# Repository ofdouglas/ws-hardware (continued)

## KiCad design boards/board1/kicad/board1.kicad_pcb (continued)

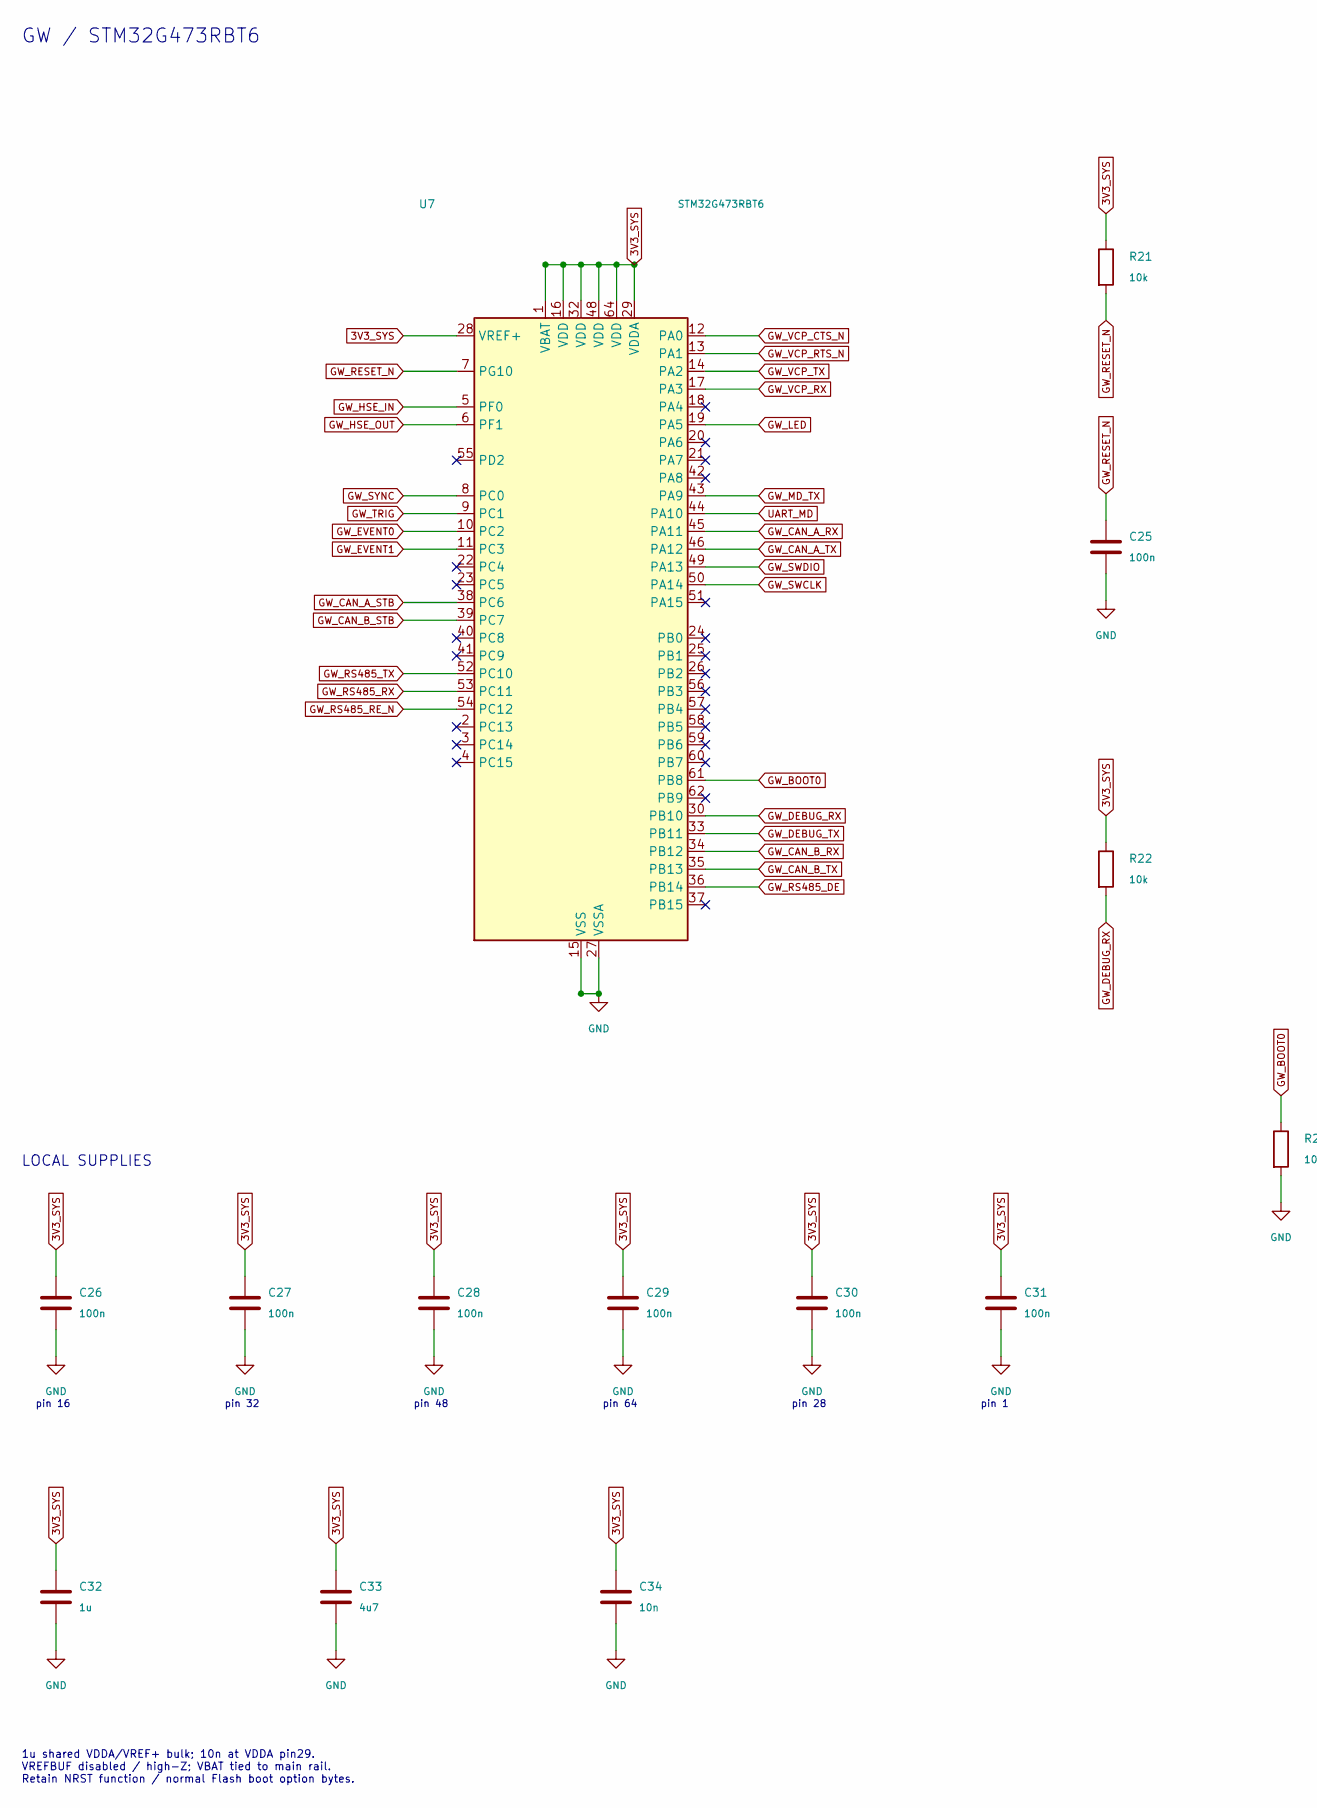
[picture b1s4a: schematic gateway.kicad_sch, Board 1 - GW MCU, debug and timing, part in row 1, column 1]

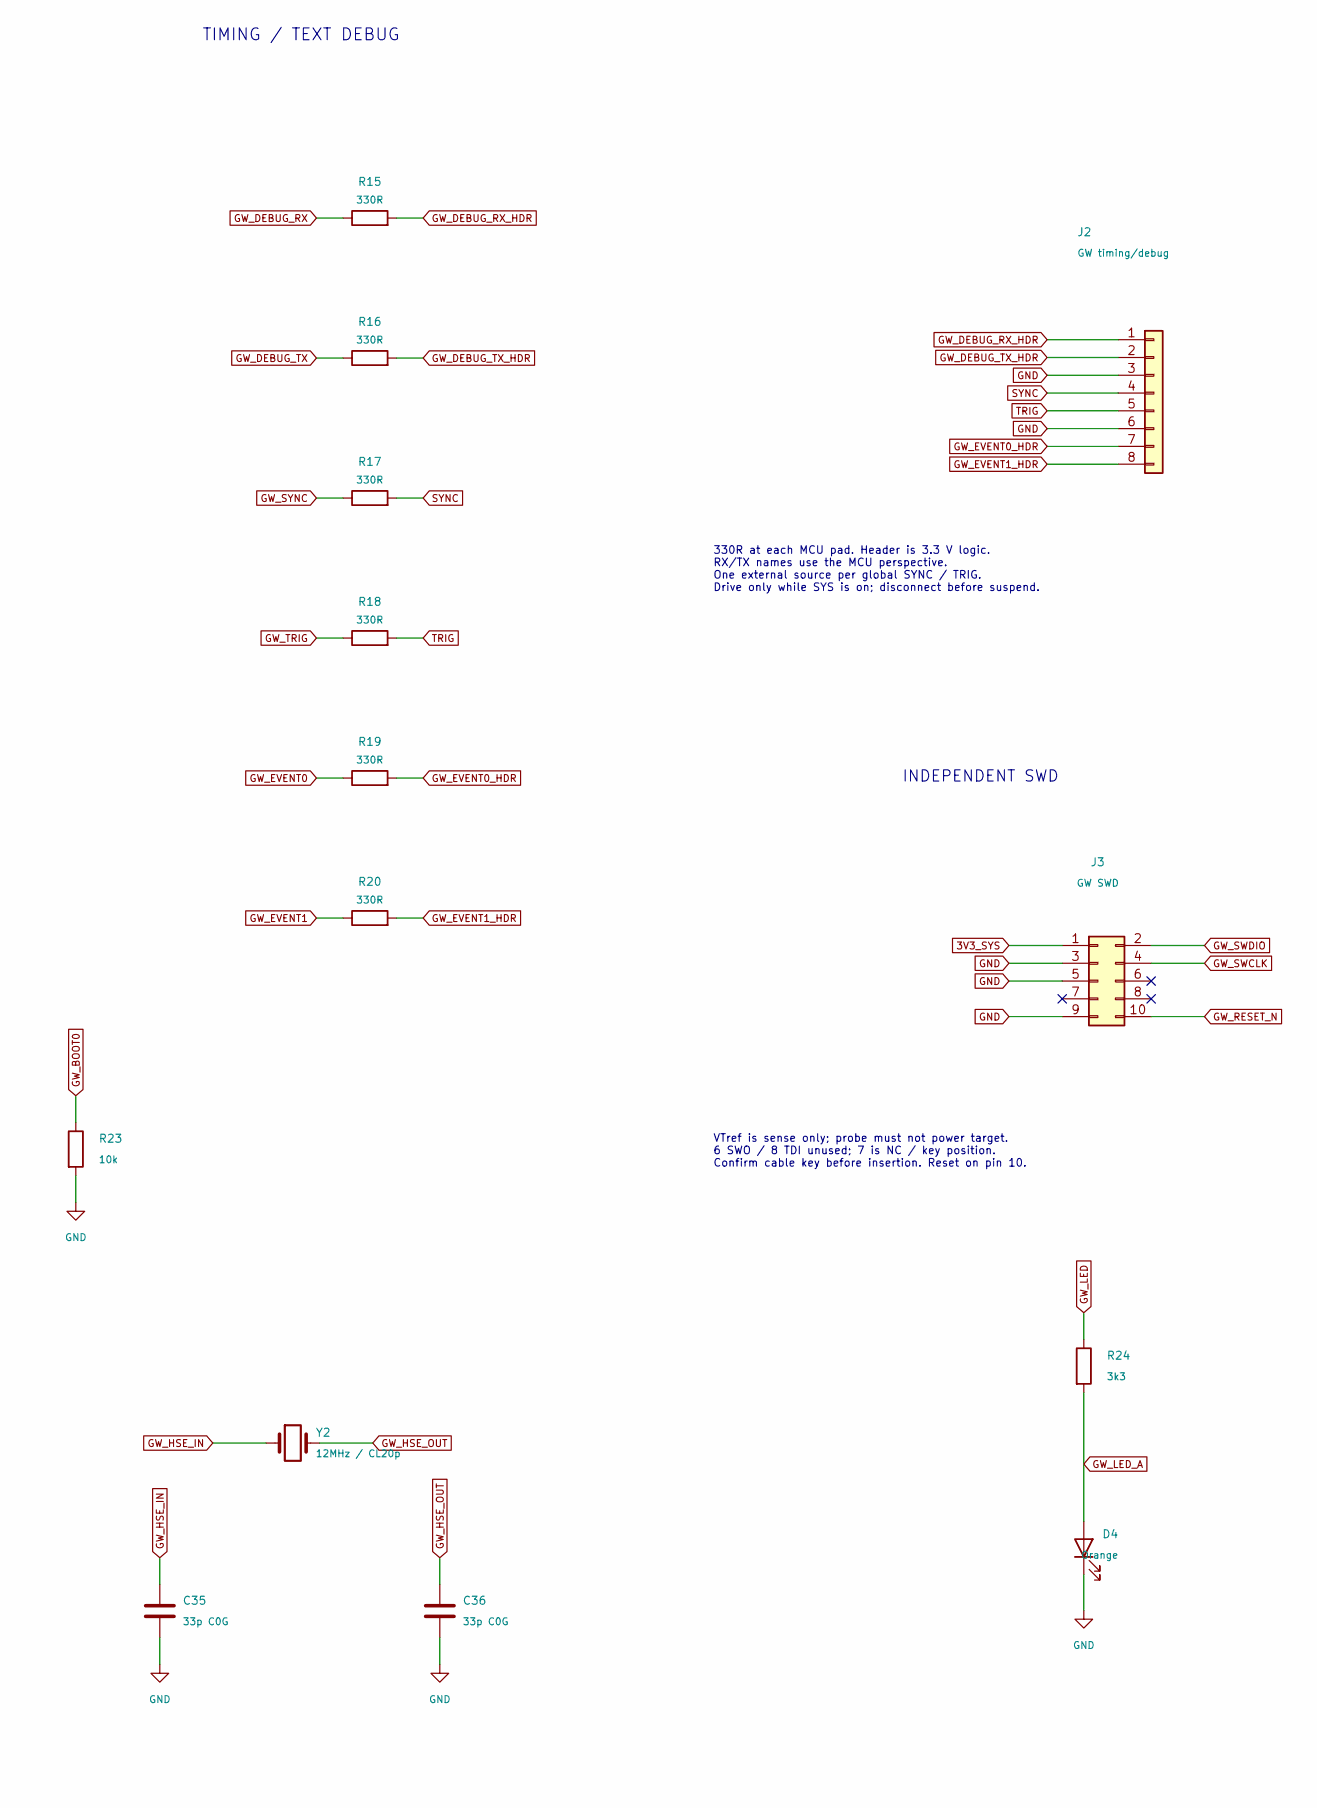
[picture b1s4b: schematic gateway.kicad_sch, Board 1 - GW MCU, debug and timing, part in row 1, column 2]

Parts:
C25, C26, C27, C28, C29, C30, C31: 100n; C_0805_2012Metric; MPN KGM21NR71E104KT
C32: 1u; C_0805_2012Metric; MPN CL21B105KAFNFNE
C33: 4u7; C_0805_2012Metric; MPN GRM21BR71C475KE51L
C34: 10n; C_0805_2012Metric; MPN CL21B103KBANNNC
C35, C36: 33p C0G; C_0805_2012Metric; MPN CC0805FRNPO9BN330
D4: Orange; LED_0603_1608Metric; MPN CSL1901DW1
J2: GW timing/debug; PinHeader_1x08_P2.54mm_Vertical; MPN PRPC040SAAN-RC
J3: GW SWD; CNC_Tech_3220-10-0100-00_2x05_P1.27mm_Vertical; MPN 3220-10-0100-00
R15, R16, R17, R18, R19, R20: 330R; R_0805_2012Metric; MPN CRGP0805F330R
R21, R22, R23: 10k; R_0805_2012Metric; MPN RMCF0805FT10K0
R24: 3k3; R_0805_2012Metric; MPN RK73H2ATTD3301F
U7: STM32G473RBT6; LQFP-64_10x10mm_P0.5mm; MPN STM32G473RBT6
Y2: 12MHz / CL20p; Crystal_SMD_ECS_CSM3X-2Pin_7.6x4.1mm; MPN ECS-120-20-3X-EN-TR

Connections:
3V3_SYS: C26.1, C27.1, C28.1, C29.1, C30.1, C31.1, C32.1, C33.1, C34.1, J3.1, R21.1, R22.1, U7.1 (VBAT), U7.16 (VDD), U7.28 (VREF+), U7.29 (VDDA), U7.32 (VDD), U7.48 (VDD), U7.64 (VDD); also elsewhere on the board
GND: C25.2, C26.2, C27.2, C28.2, C29.2, C30.2, C31.2, C32.2, C33.2, C34.2, C35.2, C36.2, D4.1 (K), J2.3, J2.6, J3.3, J3.5, J3.9, R23.2, U7.15 (VSS), U7.27 (VSSA), U7.31 (VSS), U7.47 (VSS), U7.63 (VSS); also elsewhere on the board
GW_BOOT0: R23.1, U7.61 (PB8); also elsewhere on the board
GW_CAN_A_RX: U7.45 (PA11); also elsewhere on the board
GW_CAN_A_STB: U7.38 (PC6); also elsewhere on the board
GW_CAN_A_TX: U7.46 (PA12); also elsewhere on the board
GW_CAN_B_RX: U7.34 (PB12); also elsewhere on the board
GW_CAN_B_STB: U7.39 (PC7); also elsewhere on the board
GW_CAN_B_TX: U7.35 (PB13); also elsewhere on the board
GW_DEBUG_RX: R15.1, R22.2, U7.30 (PB10)
GW_DEBUG_RX_HDR: J2.1, R15.2
GW_DEBUG_TX: R16.1, U7.33 (PB11)
GW_DEBUG_TX_HDR: J2.2, R16.2
GW_EVENT0: R19.1, U7.10 (PC2)
GW_EVENT0_HDR: J2.7, R19.2
GW_EVENT1: R20.1, U7.11 (PC3)
GW_EVENT1_HDR: J2.8, R20.2
GW_HSE_IN: C35.1, U7.5 (PF0), Y2.1
GW_HSE_OUT: C36.1, U7.6 (PF1), Y2.2
GW_LED: R24.1, U7.19 (PA5)
GW_LED_A: D4.2 (A), R24.2
GW_MD_TX: U7.43 (PA9); also elsewhere on the board
GW_RESET_N: C25.1, J3.10, R21.2, U7.7 (PG10); also elsewhere on the board
GW_RS485_DE: U7.36 (PB14); also elsewhere on the board
GW_RS485_RE_N: U7.54 (PC12); also elsewhere on the board
GW_RS485_RX: U7.53 (PC11); also elsewhere on the board
GW_RS485_TX: U7.52 (PC10); also elsewhere on the board
GW_SWCLK: J3.4, U7.50 (PA14)
GW_SWDIO: J3.2, U7.49 (PA13)
GW_SYNC: R17.1, U7.8 (PC0)
GW_TRIG: R18.1, U7.9 (PC1)
GW_VCP_CTS_N: U7.12 (PA0); also elsewhere on the board
GW_VCP_RTS_N: U7.13 (PA1); also elsewhere on the board
GW_VCP_RX: U7.17 (PA3); also elsewhere on the board
GW_VCP_TX: U7.14 (PA2); also elsewhere on the board
SYNC: J2.4, R17.2; also elsewhere on the board
TRIG: J2.5, R18.2; also elsewhere on the board
UART_MD: U7.44 (PA10); also elsewhere on the board

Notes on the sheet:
GW / STM32G473RBT6
TIMING / TEXT DEBUG
INDEPENDENT SWD
330R at each MCU pad. Header is 3.3 V logic. RX/TX names use the MCU perspective. One external source per global SYNC / TRIG. Drive only while SYS is on; disconnect before suspend.
VTref is sense only; probe must not power target. 6 SWO / 8 TDI unused; 7 is NC / key position. Confirm cable key before insertion. Reset on pin 10.
LOCAL SUPPLIES
pin 16
pin 32
pin 48
pin 64
pin 28
pin 1
1u shared VDDA/VREF+ bulk; 10n at VDDA pin29. VREFBUF disabled / high-Z; VBAT tied to main rail. Retain NRST function / normal Flash boot option bytes.

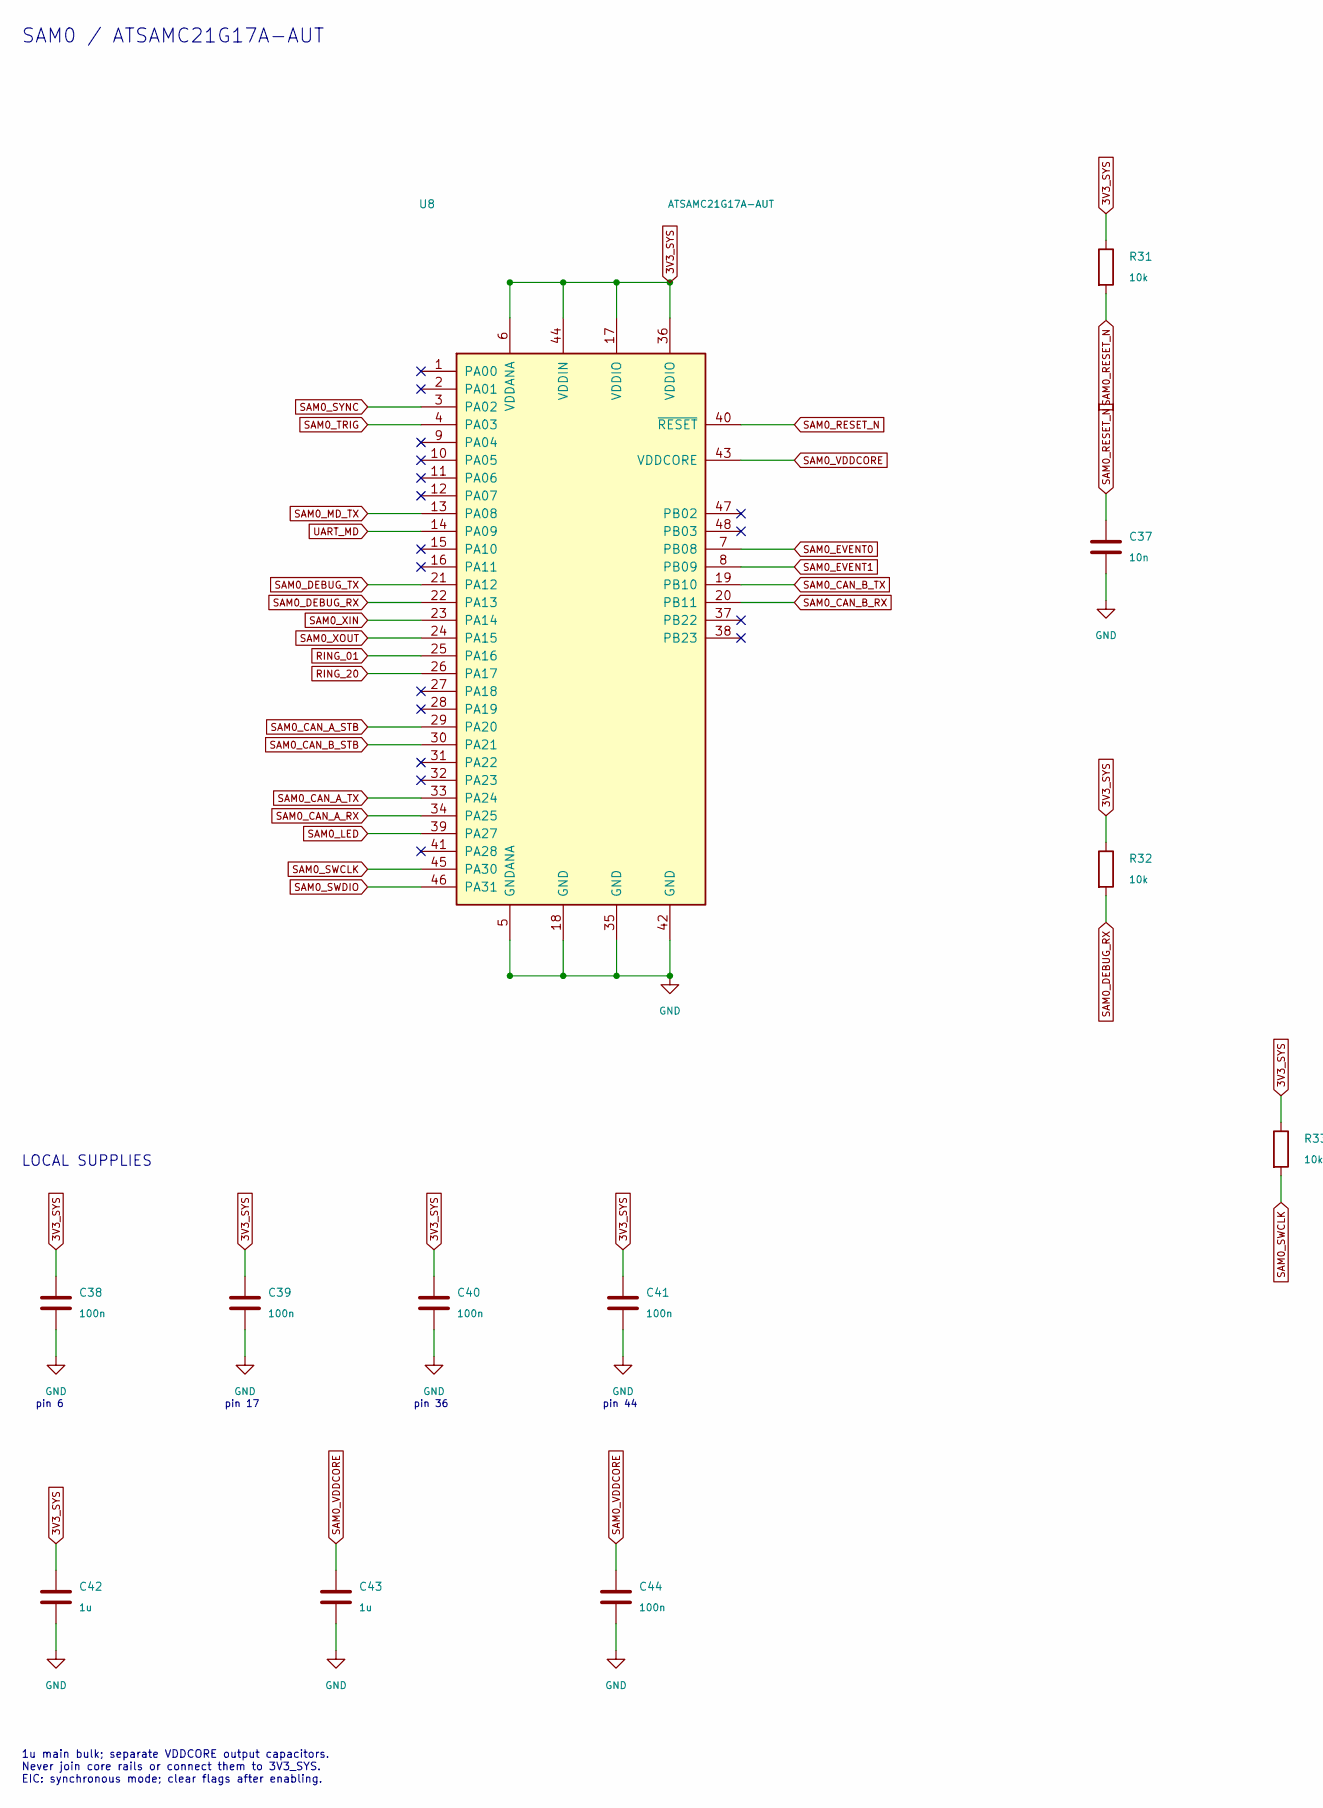
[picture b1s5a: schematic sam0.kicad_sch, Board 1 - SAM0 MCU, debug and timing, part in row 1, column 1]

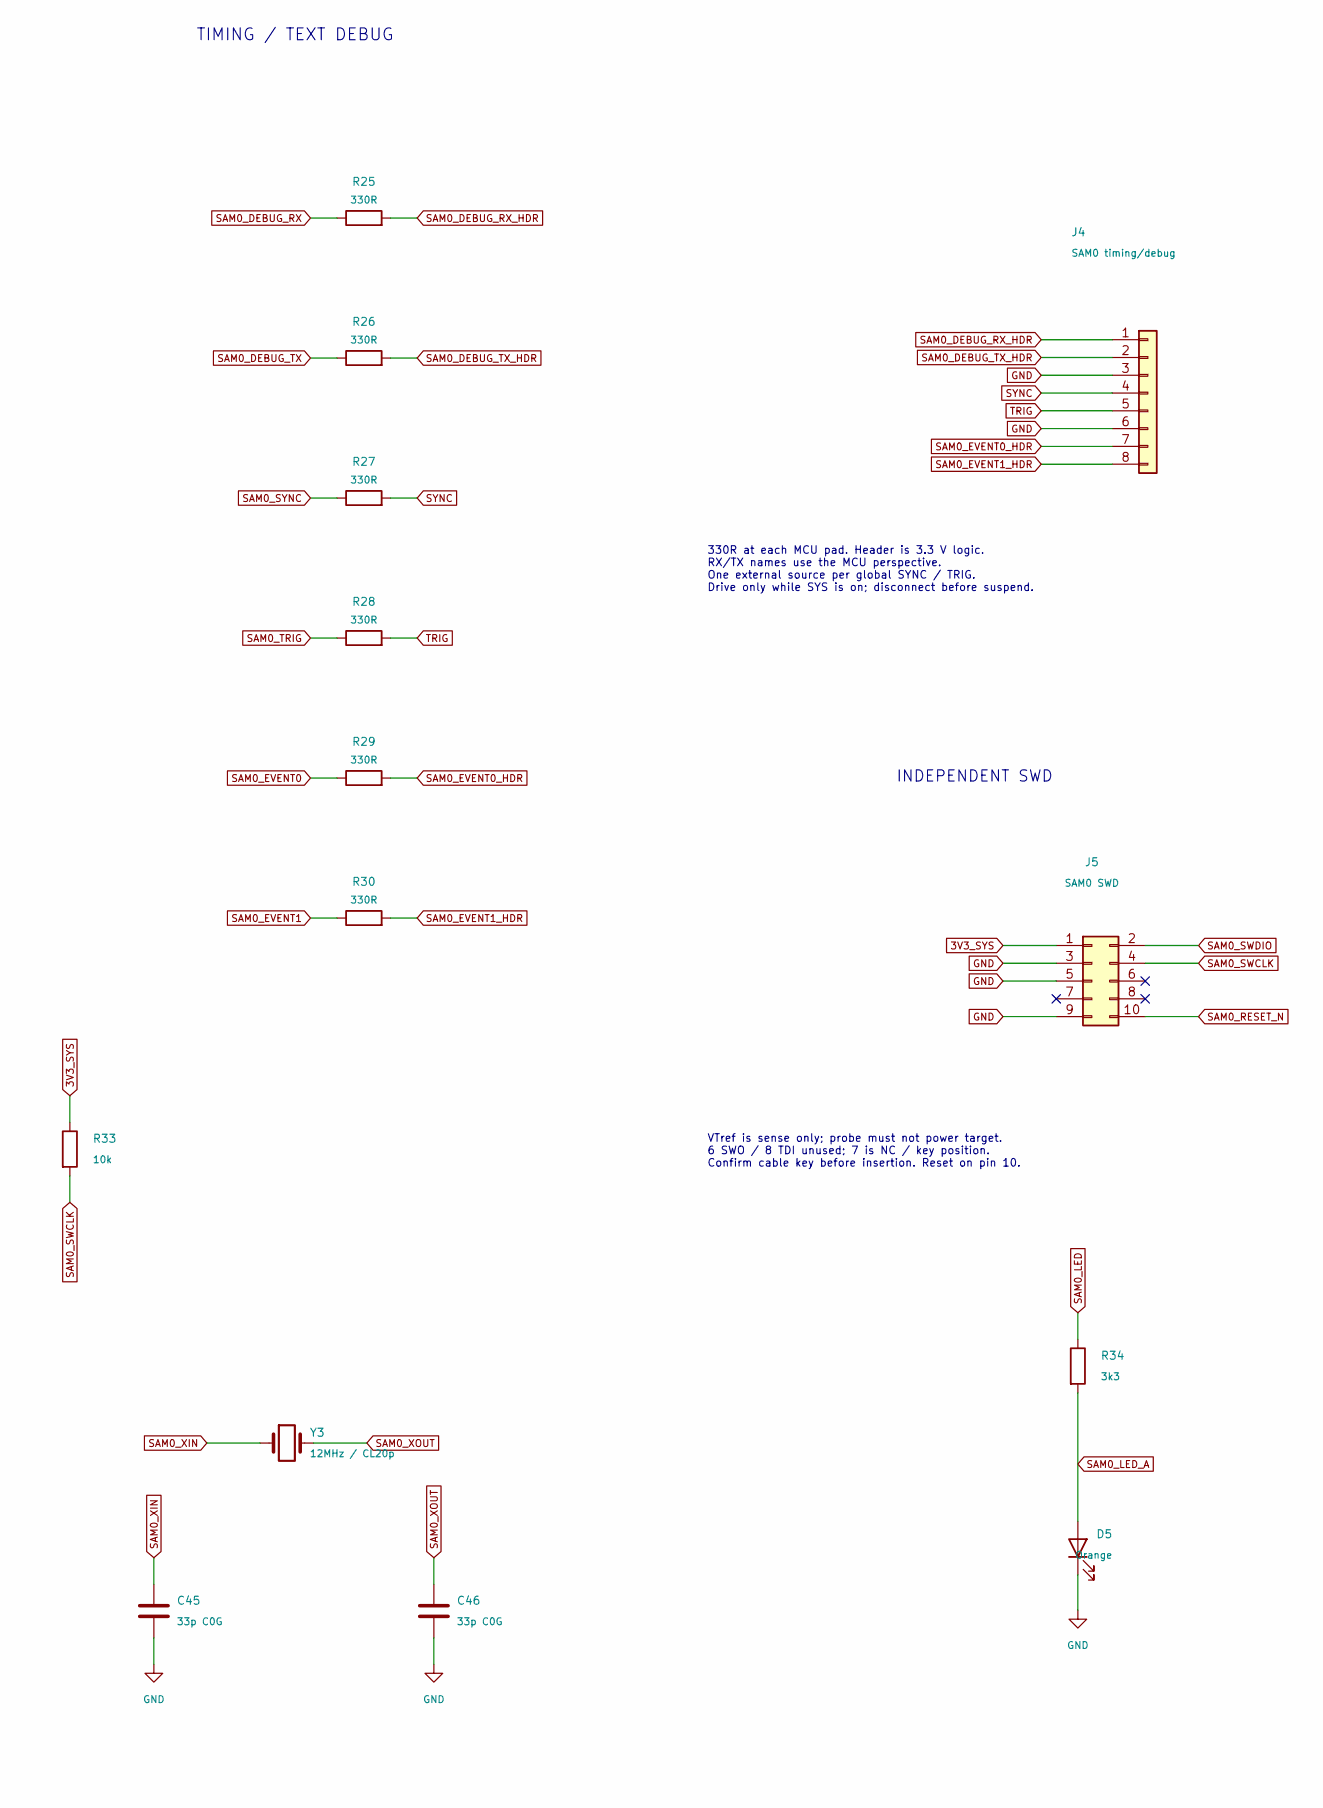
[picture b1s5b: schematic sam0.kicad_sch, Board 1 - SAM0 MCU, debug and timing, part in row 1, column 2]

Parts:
C37: 10n; C_0805_2012Metric; MPN CL21B103KBANNNC
C38, C39, C40, C41, C44: 100n; C_0805_2012Metric; MPN KGM21NR71E104KT
C42, C43: 1u; C_0805_2012Metric; MPN CL21B105KAFNFNE
C45, C46: 33p C0G; C_0805_2012Metric; MPN CC0805FRNPO9BN330
D5: Orange; LED_0603_1608Metric; MPN CSL1901DW1
J4: SAM0 timing/debug; PinHeader_1x08_P2.54mm_Vertical; MPN PRPC040SAAN-RC
J5: SAM0 SWD; CNC_Tech_3220-10-0100-00_2x05_P1.27mm_Vertical; MPN 3220-10-0100-00
R25, R26, R27, R28, R29, R30: 330R; R_0805_2012Metric; MPN CRGP0805F330R
R31, R32, R33: 10k; R_0805_2012Metric; MPN RMCF0805FT10K0
R34: 3k3; R_0805_2012Metric; MPN RK73H2ATTD3301F
U8: ATSAMC21G17A-AUT; TQFP-48_7x7mm_P0.5mm; MPN ATSAMC21G17A-AUT
Y3: 12MHz / CL20p; Crystal_SMD_ECS_CSM3X-2Pin_7.6x4.1mm; MPN ECS-120-20-3X-EN-TR

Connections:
3V3_SYS: C38.1, C39.1, C40.1, C41.1, C42.1, J5.1, R31.1, R32.1, R33.1, U8.6 (VDDANA), U8.17 (VDDIO), U8.36 (VDDIO), U8.44 (VDDIN); also elsewhere on the board
GND: C37.2, C38.2, C39.2, C40.2, C41.2, C42.2, C43.2, C44.2, C45.2, C46.2, D5.1 (K), J4.3, J4.6, J5.3, J5.5, J5.9, U8.5 (GNDANA), U8.18 (GND), U8.35 (GND), U8.42 (GND); also elsewhere on the board
RING_01: U8.25 (PA16); also elsewhere on the board
RING_20: U8.26 (PA17); also elsewhere on the board
SAM0_CAN_A_RX: U8.34 (PA25); also elsewhere on the board
SAM0_CAN_A_STB: U8.29 (PA20); also elsewhere on the board
SAM0_CAN_A_TX: U8.33 (PA24); also elsewhere on the board
SAM0_CAN_B_RX: U8.20 (PB11); also elsewhere on the board
SAM0_CAN_B_STB: U8.30 (PA21); also elsewhere on the board
SAM0_CAN_B_TX: U8.19 (PB10); also elsewhere on the board
SAM0_DEBUG_RX: R25.1, R32.2, U8.22 (PA13)
SAM0_DEBUG_RX_HDR: J4.1, R25.2
SAM0_DEBUG_TX: R26.1, U8.21 (PA12)
SAM0_DEBUG_TX_HDR: J4.2, R26.2
SAM0_EVENT0: R29.1, U8.7 (PB08)
SAM0_EVENT0_HDR: J4.7, R29.2
SAM0_EVENT1: R30.1, U8.8 (PB09)
SAM0_EVENT1_HDR: J4.8, R30.2
SAM0_LED: R34.1, U8.39 (PA27)
SAM0_LED_A: D5.2 (A), R34.2
SAM0_MD_TX: U8.13 (PA08); also elsewhere on the board
SAM0_RESET_N: C37.1, J5.10, R31.2, U8.40 (~RESET); also elsewhere on the board
SAM0_SWCLK: J5.4, R33.2, U8.45 (PA30)
SAM0_SWDIO: J5.2, U8.46 (PA31)
SAM0_SYNC: R27.1, U8.3 (PA02)
SAM0_TRIG: R28.1, U8.4 (PA03)
SAM0_VDDCORE: C43.1, C44.1, U8.43 (VDDCORE); also elsewhere on the board
SAM0_XIN: C45.1, U8.23 (PA14), Y3.1
SAM0_XOUT: C46.1, U8.24 (PA15), Y3.2
SYNC: J4.4, R27.2; also elsewhere on the board
TRIG: J4.5, R28.2; also elsewhere on the board
UART_MD: U8.14 (PA09); also elsewhere on the board

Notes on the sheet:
SAM0 / ATSAMC21G17A-AUT
TIMING / TEXT DEBUG
INDEPENDENT SWD
330R at each MCU pad. Header is 3.3 V logic. RX/TX names use the MCU perspective. One external source per global SYNC / TRIG. Drive only while SYS is on; disconnect before suspend.
VTref is sense only; probe must not power target. 6 SWO / 8 TDI unused; 7 is NC / key position. Confirm cable key before insertion. Reset on pin 10.
LOCAL SUPPLIES
pin 6
pin 17
pin 36
pin 44
1u main bulk; separate VDDCORE output capacitors. Never join core rails or connect them to 3V3_SYS. EIC: synchronous mode; clear flags after enabling.

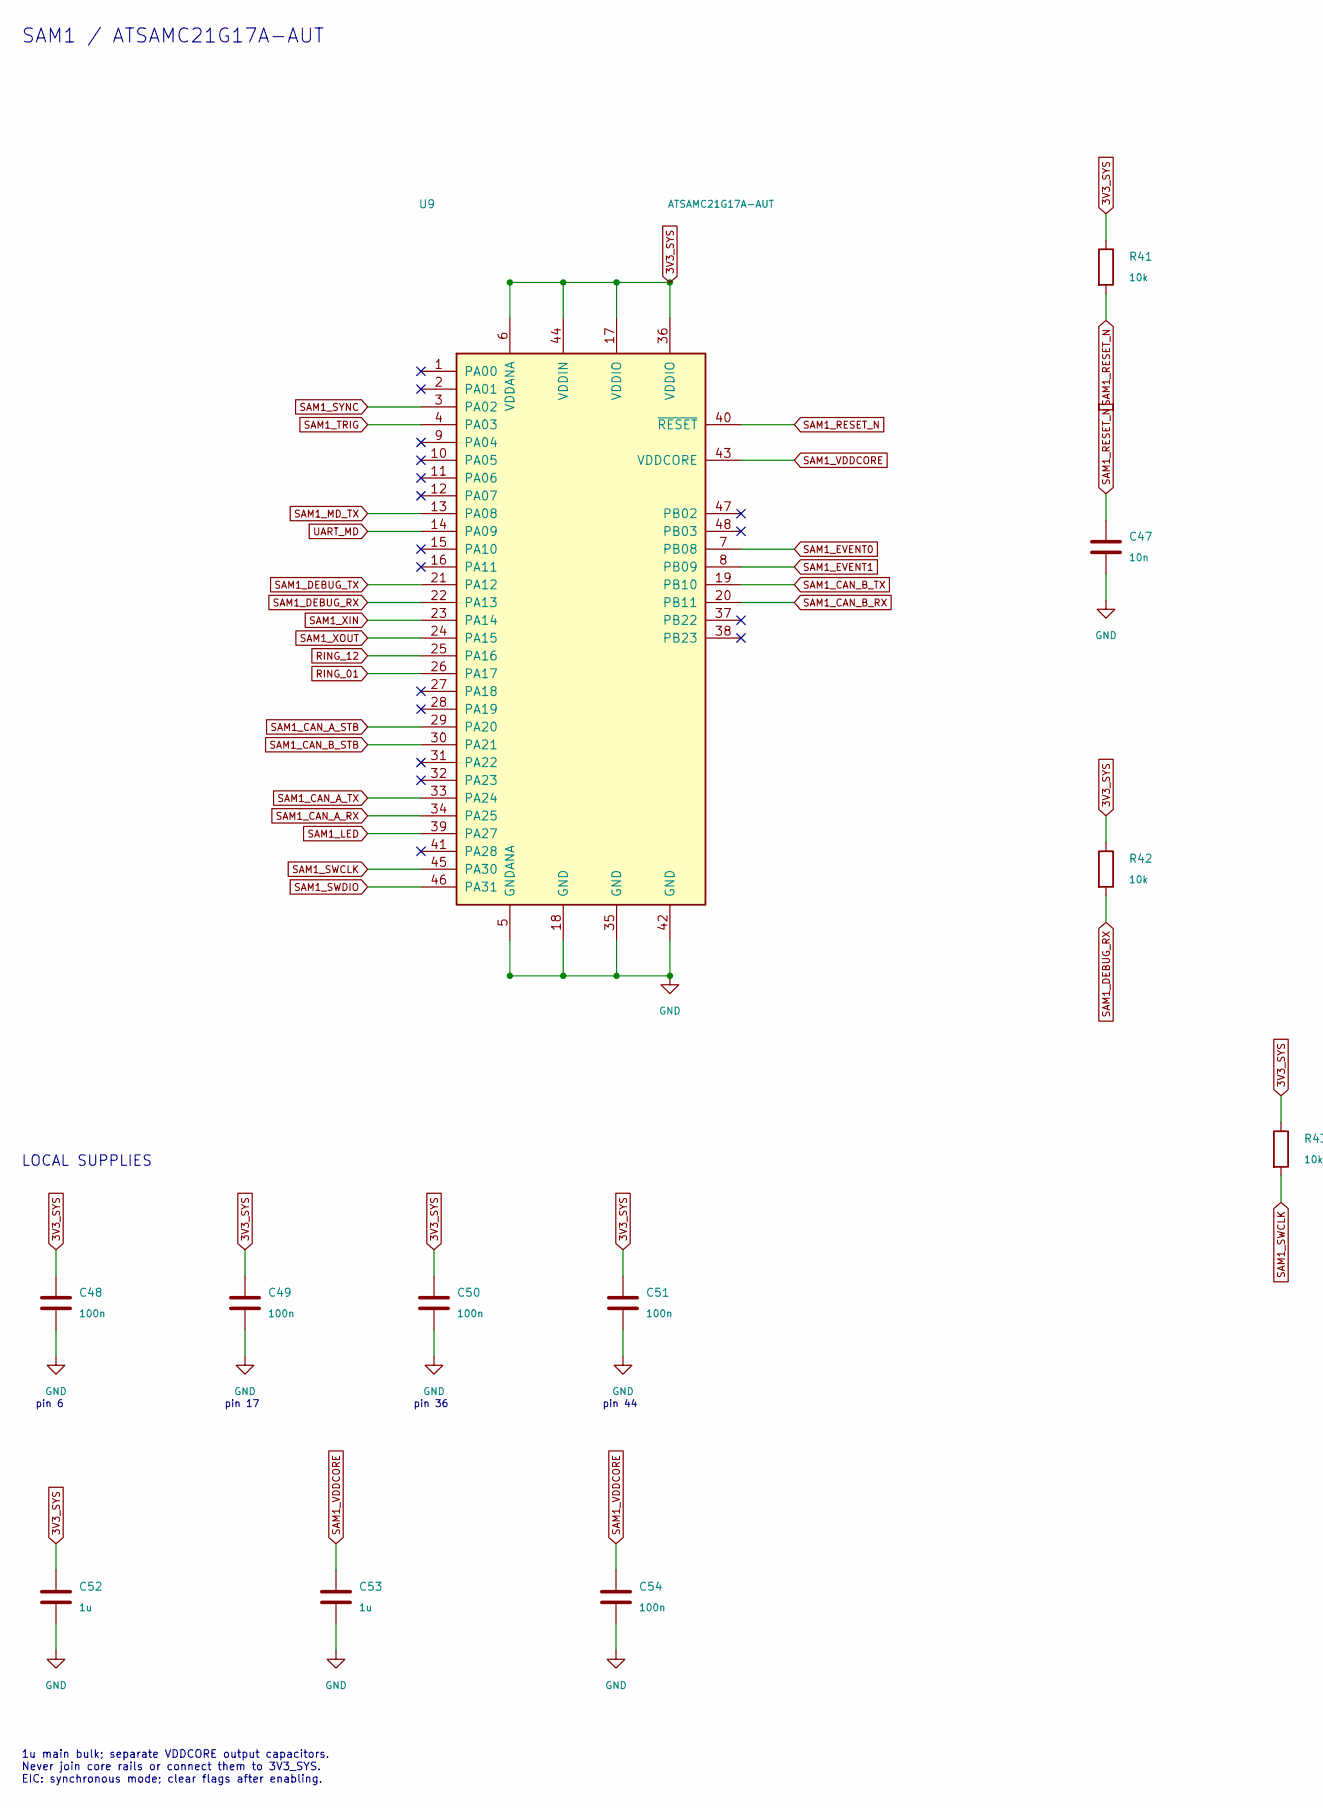
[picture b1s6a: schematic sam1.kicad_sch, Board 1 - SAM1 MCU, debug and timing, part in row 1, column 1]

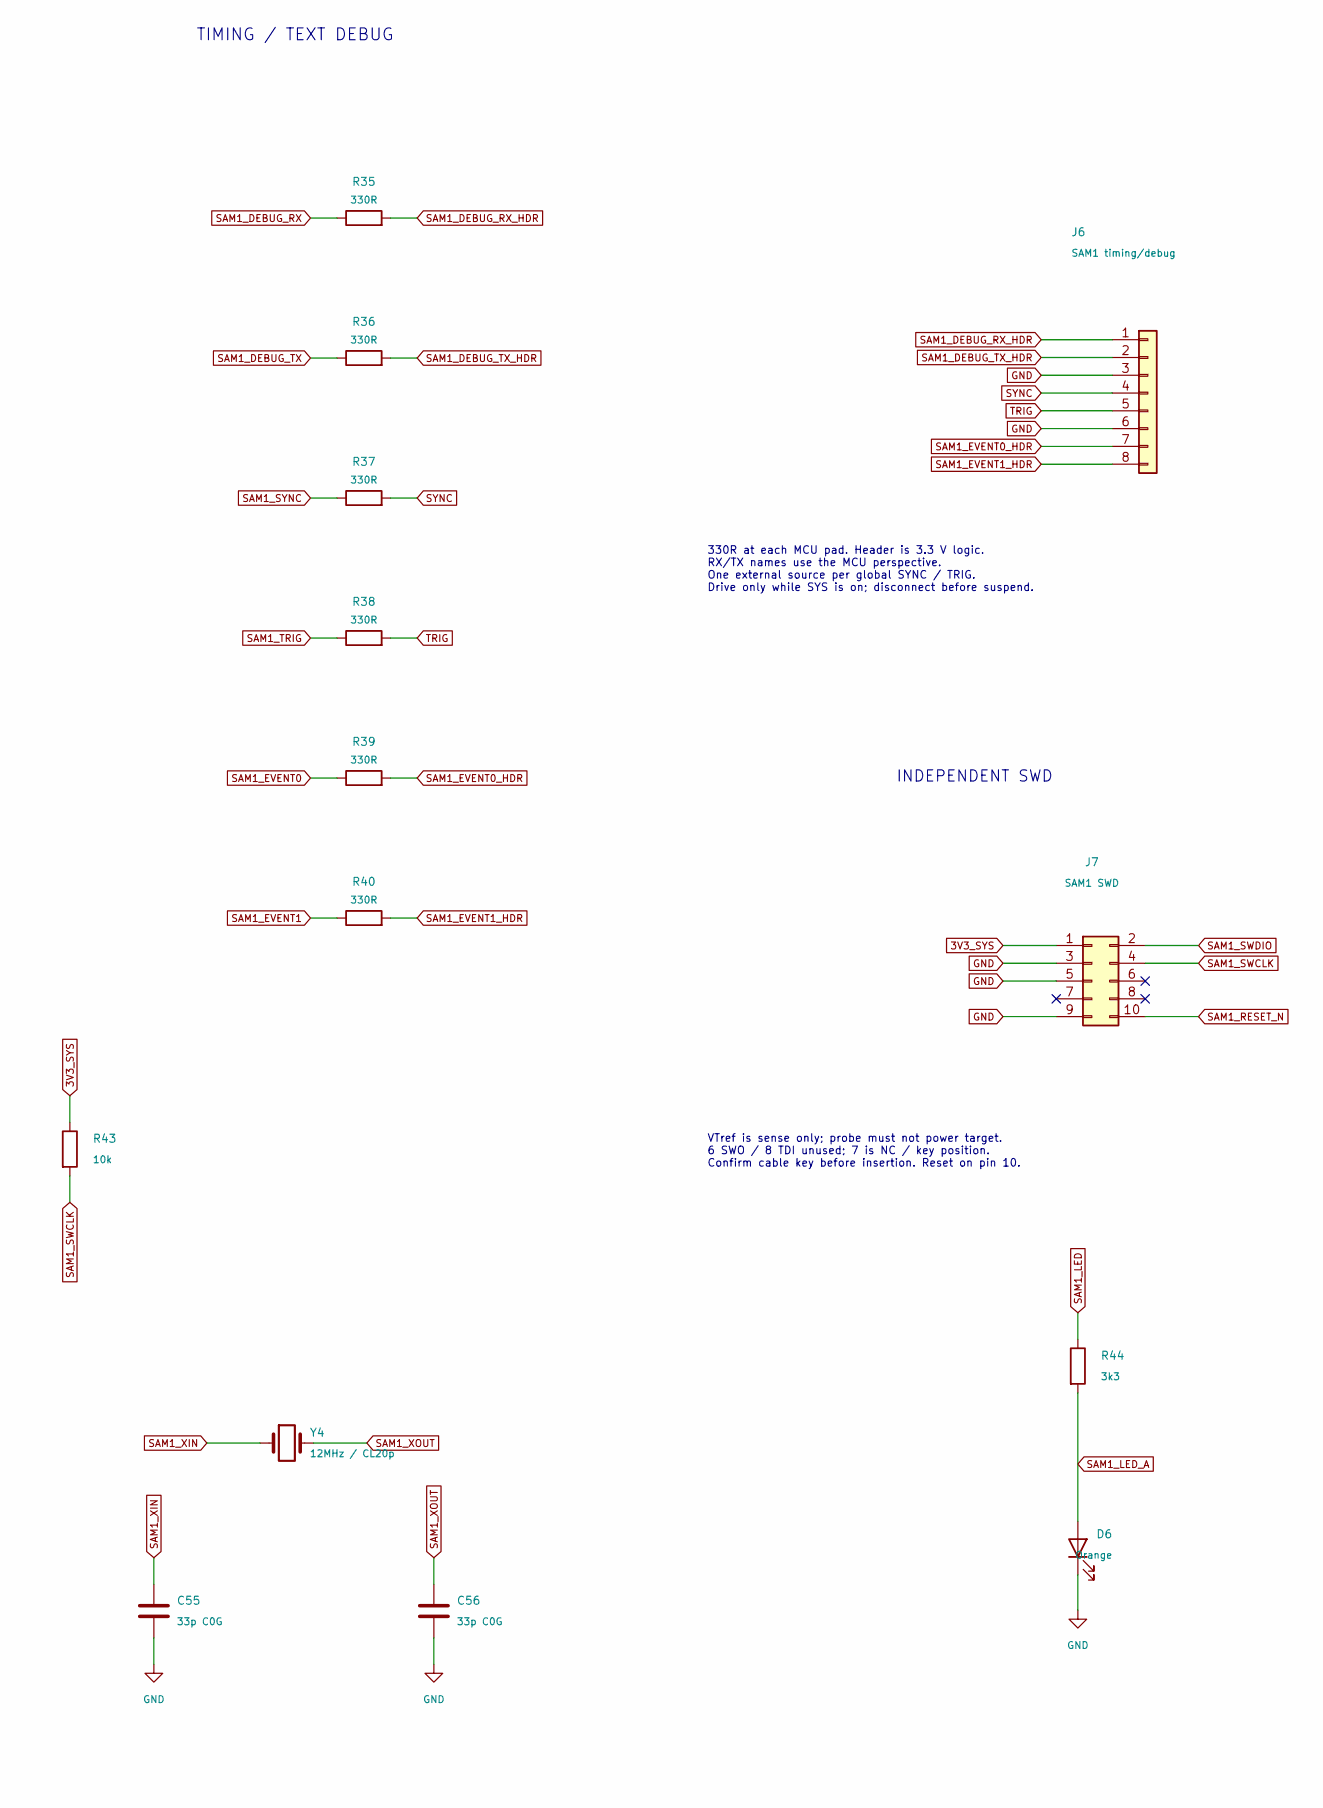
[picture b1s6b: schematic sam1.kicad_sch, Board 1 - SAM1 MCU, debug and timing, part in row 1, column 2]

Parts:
C47: 10n; C_0805_2012Metric; MPN CL21B103KBANNNC
C48, C49, C50, C51, C54: 100n; C_0805_2012Metric; MPN KGM21NR71E104KT
C52, C53: 1u; C_0805_2012Metric; MPN CL21B105KAFNFNE
C55, C56: 33p C0G; C_0805_2012Metric; MPN CC0805FRNPO9BN330
D6: Orange; LED_0603_1608Metric; MPN CSL1901DW1
J6: SAM1 timing/debug; PinHeader_1x08_P2.54mm_Vertical; MPN PRPC040SAAN-RC
J7: SAM1 SWD; CNC_Tech_3220-10-0100-00_2x05_P1.27mm_Vertical; MPN 3220-10-0100-00
R35, R36, R37, R38, R39, R40: 330R; R_0805_2012Metric; MPN CRGP0805F330R
R41, R42, R43: 10k; R_0805_2012Metric; MPN RMCF0805FT10K0
R44: 3k3; R_0805_2012Metric; MPN RK73H2ATTD3301F
U9: ATSAMC21G17A-AUT; TQFP-48_7x7mm_P0.5mm; MPN ATSAMC21G17A-AUT
Y4: 12MHz / CL20p; Crystal_SMD_ECS_CSM3X-2Pin_7.6x4.1mm; MPN ECS-120-20-3X-EN-TR

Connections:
3V3_SYS: C48.1, C49.1, C50.1, C51.1, C52.1, J7.1, R41.1, R42.1, R43.1, U9.6 (VDDANA), U9.17 (VDDIO), U9.36 (VDDIO), U9.44 (VDDIN); also elsewhere on the board
GND: C47.2, C48.2, C49.2, C50.2, C51.2, C52.2, C53.2, C54.2, C55.2, C56.2, D6.1 (K), J6.3, J6.6, J7.3, J7.5, J7.9, U9.5 (GNDANA), U9.18 (GND), U9.35 (GND), U9.42 (GND); also elsewhere on the board
RING_01: U9.26 (PA17); also elsewhere on the board
RING_12: U9.25 (PA16); also elsewhere on the board
SAM1_CAN_A_RX: U9.34 (PA25); also elsewhere on the board
SAM1_CAN_A_STB: U9.29 (PA20); also elsewhere on the board
SAM1_CAN_A_TX: U9.33 (PA24); also elsewhere on the board
SAM1_CAN_B_RX: U9.20 (PB11); also elsewhere on the board
SAM1_CAN_B_STB: U9.30 (PA21); also elsewhere on the board
SAM1_CAN_B_TX: U9.19 (PB10); also elsewhere on the board
SAM1_DEBUG_RX: R35.1, R42.2, U9.22 (PA13)
SAM1_DEBUG_RX_HDR: J6.1, R35.2
SAM1_DEBUG_TX: R36.1, U9.21 (PA12)
SAM1_DEBUG_TX_HDR: J6.2, R36.2
SAM1_EVENT0: R39.1, U9.7 (PB08)
SAM1_EVENT0_HDR: J6.7, R39.2
SAM1_EVENT1: R40.1, U9.8 (PB09)
SAM1_EVENT1_HDR: J6.8, R40.2
SAM1_LED: R44.1, U9.39 (PA27)
SAM1_LED_A: D6.2 (A), R44.2
SAM1_MD_TX: U9.13 (PA08); also elsewhere on the board
SAM1_RESET_N: C47.1, J7.10, R41.2, U9.40 (~RESET); also elsewhere on the board
SAM1_SWCLK: J7.4, R43.2, U9.45 (PA30)
SAM1_SWDIO: J7.2, U9.46 (PA31)
SAM1_SYNC: R37.1, U9.3 (PA02)
SAM1_TRIG: R38.1, U9.4 (PA03)
SAM1_VDDCORE: C53.1, C54.1, U9.43 (VDDCORE); also elsewhere on the board
SAM1_XIN: C55.1, U9.23 (PA14), Y4.1
SAM1_XOUT: C56.1, U9.24 (PA15), Y4.2
SYNC: J6.4, R37.2; also elsewhere on the board
TRIG: J6.5, R38.2; also elsewhere on the board
UART_MD: U9.14 (PA09); also elsewhere on the board

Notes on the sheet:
SAM1 / ATSAMC21G17A-AUT
TIMING / TEXT DEBUG
INDEPENDENT SWD
330R at each MCU pad. Header is 3.3 V logic. RX/TX names use the MCU perspective. One external source per global SYNC / TRIG. Drive only while SYS is on; disconnect before suspend.
VTref is sense only; probe must not power target. 6 SWO / 8 TDI unused; 7 is NC / key position. Confirm cable key before insertion. Reset on pin 10.
LOCAL SUPPLIES
pin 6
pin 17
pin 36
pin 44
1u main bulk; separate VDDCORE output capacitors. Never join core rails or connect them to 3V3_SYS. EIC: synchronous mode; clear flags after enabling.

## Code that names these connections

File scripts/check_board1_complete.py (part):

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    require(len({net('U4', p) for p in [37, 38, 39, 40]}) == 4,
            'FTDI VCCA/VCORE/VCCD/VREGIN must be four separate rails')
    for pin in [1, 4, 10, 13]:
        named('U6', pin, 'PWREN_N')
    named('D1', 1, 'VBUS_RAW')
    named('D1', 2, 'GND')
    for pin in [5, 6]:
        named('U1', pin, 'USB_5V')
    named('U2', 3, '3V3_SYS')
    named('L1', 2, '3V3_SYS')
    gateway = parts('B1-B001', 1)[0]
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        named(header, 5, 'TRIG')
        for pin, suffix in {1: 'DEBUG_RX', 2: 'DEBUG_TX', 7: 'EVENT0', 8: 'EVENT1'}.items():
            named(header, pin, f'{owner}_{suffix}_HDR')
        for pin, suffix in {1: 'DEBUG_RX', 2: 'DEBUG_TX', 4: 'SYNC', 5: 'TRIG', 7: 'EVENT0', 8: 'EVENT1'}.items():
            other = f'{owner}_{suffix}'
            matching = [r for r in series if {net(r, 1).rsplit('/', 1)[-1], net(r, 2).rsplit('/', 1)[-1]}
                        == {net(header, pin).rsplit('/', 1)[-1], other}]
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        for pin in [2, 5, 9, 12, 7]:
            named(ref, pin, 'GND')
        for pin in [3, 6, 8, 11]:
            named(ref, pin, 'UART_MD')
        named(ref, 14, '3V3_SYS')
        require(len({net(ref, p) for p in [1, 4, 10, 13]}) == 4,
                'UART_MD output enables must have four independent MCU TX signals')
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    tvs_buses = set()
    for ref in parts('B1-B072', 2):
        h = net(ref, 1).rsplit('/', 1)[-1]
        require(h in {'FD_CAN_A_H', 'FD_CAN_B_H'}, f'{ref}: CAN TVS pin 1 must connect directly to CANH')
        bus = h.removeprefix('FD_CAN_').removesuffix('_H')
        tvs_buses.add(bus)
        named(ref, 2, f'FD_CAN_{bus}_L')
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    require(tvs_buses == {'A', 'B'}, 'CAN TVS arrays must cover both terminal pairs')

    phy = parts('B1-B021', 1)[0]
    for pin, signal in {1: 'GW_RS485_RX', 2: 'GW_RS485_RE_N', 3: 'GW_RS485_DE',
                        4: 'GW_RS485_TX', 5: 'GND', 6: 'RS485_A', 7: 'RS485_B', 8: '3V3_SYS'}.items():
        named(phy, pin, signal)
    require(endpoints(parts('B1-B068', 1)[0]) == {'RS485_A', 'RS485_B'},
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    require(biases == {frozenset({'3V3_SYS', 'RS485_A'}), frozenset({'RS485_B', 'GND'})},
            'RS-485 idle bias polarity must be A high / B low')
    tvs = parts('B1-B073', 1)[0]
    for pin, signal in {1: 'RS485_A', 2: 'RS485_B', 3: 'GND'}.items():
        named(tvs, pin, signal)
    terminal = parts('B1-B022', 1)[0]
    for pin, signal in enumerate(['FD_CAN_A_H', 'FD_CAN_A_L', 'GND', 'FD_CAN_B_H',
                                   'FD_CAN_B_L', 'RS485_A', 'RS485_B', 'GND'], 1):
        named(terminal, pin, signal)
    connectors = {ref for ref, spec in expected.items()
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
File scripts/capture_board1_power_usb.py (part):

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    s.wire(s.pt('J1',1),(150,rail_y),s.pt('U1',1))
    for ref in ['D1','C1','R1']:
        a=s.pt(ref,1);s.wire(a,(a[0],rail_y));s.junction((a[0],rail_y));s.mark(ref,[1],'VBUS_RAW')
    s.label('VBUS_RAW',(80,rail_y))
    s.wire(s.pt('U1',3),(150,65),(150,rail_y));s.junction((150,rail_y));s.mark('J1',[1],'VBUS_RAW');s.mark('U1',[1,3],'VBUS_RAW')
    s.wire(s.pt('R1',2),s.pt('C2',1));s.mark('R1',[2],'VBUS_DAMP');s.mark('C2',[1],'VBUS_DAMP')
    s.label('VBUS_DAMP',(120,92))
    for ref,pin in [('D1',2),('C1',2),('C2',2),('C3',2),('U1',2)]:s.net(ref,pin,'GND',5.08)
    s.wire(s.pt('J1',5),(32.46,82),(35,82),s.pt('J1',4));s.ground((35,82));s.mark('J1',[4,5],'GND')
    s.wire(s.pt('U1',4),(150,70.08),s.pt('C3',1));s.mark('U1',[4],'IN_CT');s.mark('C3',[1],'IN_CT');s.label('IN_CT',(150,80))
    s.wire(s.pt('U1',6),(245,rail_y));s.wire(s.pt('U1',5),(205,65),(205,rail_y));s.junction((205,rail_y));s.mark('U1',[5,6],'USB_5V');s.label('USB_5V',(215,rail_y),glob=True)
    for ref,x,bid,v in [('C4',220,'B1-B063','4u7'),('C5',243,'B1-B061','100n')]:
        s.symbol('Device:C',ref,x,85,bid,val=v,fp=CAP);s.wire(s.pt(ref,1),(x,rail_y));s.junction((x,rail_y));s.mark(ref,[1],'USB_5V');s.net(ref,2,'GND',5.08)
    s.text('C4/C5: place at FTDI VREGIN (U4 pin 40).',205,104,1.15)
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    s.symbol('Device:C','C8',327.94,48,'B1-B031',val='100n',angle=90,fp=CAP)
    s.wire(s.pt('U2',1),(315.24,48),s.pt('C8',1));s.mark('U2',[1],'BUCK_CB');s.mark('C8',[1],'BUCK_CB')
    s.wire(s.pt('C8',2),(335.28,48),(335.28,65));s.junction((335.28,65));s.mark('C8',[2],'BUCK_SW')
    s.label('BUCK_SW',(319,65));s.label('BUCK_CB',(315.24,48))
    s.wire(s.pt('L1',2),(380,65));s.mark('L1',[2],'3V3_SYS');s.label('3V3_SYS',(380,65),glob=True)
    s.symbol('Device:C','C7',375,85,'B1-B030',val='22u / 16V',fp=C1210);s.wire(s.pt('C7',1),(375,65));s.mark('C7',[1],'3V3_SYS');s.junction((375,65));s.net('C7',2,'GND')
    s.wire(s.pt('U2',3),(365,70.08),(365,65));s.junction((365,65));s.mark('U2',[3],'3V3_SYS');s.net('U2',2,'GND')
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    s.text('POWER INDICATOR',343,133,1.5)
    s.symbol('Device:R','R4',360,158,'B1-B026',val='3k3',fp=RES);s.net('R4',1,'3V3_SYS',5.08,True)
    s.symbol('Device:LED','D3',360,177,'B1-B025',val='Orange',angle=90,fp='LED_SMD:LED_0603_1608Metric',show=((364,175),(364,178),'left'))
    s.wire(s.pt('R4',2),s.pt('D3',2));s.mark('R4',[2],'PWR_LED_A');s.mark('D3',[2],'PWR_LED_A');s.label('PWR_LED_A',(360,168));s.net('D3',1,'GND',5.08)
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    s.text('USB_5V / USB_DM / USB_DP\nFTDI_3V3 / PWREN_N / 3V3_SYS\nCross-sheet connections use named global nets.',30,229,1.25)
    s.text('USB-only, active-PC bench operation. 500 mA configured input budget.\nPower/USB capture ends at GW_VCP_TX/RX/RTS_N/CTS_N.\nMCU, CAN, RS-485 and timing-header sections are not captured.\nNo external reset supervisor or CBUS recovery circuitry.',155,222,1.3)
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    cap(s,'C12',20,155,'B1-B058','27p C0G','XTIN',glob=False);cap(s,'C13',48,155,'B1-B058','27p C0G','XTOUT',glob=False)
    s.symbol('Device:R','R5',25,58,'B1-B051',val='10k',fp=RES);s.net('R5',1,'FTDI_3V3',3.81,True)
    s.symbol('Device:C','C14',25,91,'B1-B064',val='10n',fp=CAP);s.net('C14',2,'GND',3.81)
    s.wire(s.pt('R5',2),s.pt('C14',1));s.label('FTDI_RESET_N',(25,75));s.mark('R5',[2],'FTDI_RESET_N');s.mark('C14',[1],'FTDI_RESET_N')
    s.passive('R','R6',47,91,'B1-B057','12k 1%','FTDI_REF','GND',fp=RES)
    s.symbol('AT93C56B-SSHM-B:AT93C56B-SSHM-B','U5',215,75,'B1-B013',show=((228,44),(228,47),''))
    for p,n in {1:'EECS',2:'EECLK',3:'EEDATA',6:'FTDI_3V3',8:'FTDI_3V3'}.items():s.net('U5',p,n,7.62,p in[6,8])
    s.net('U5',5,'GND');s.noconnect('U5',7)
    s.symbol('Device:R','R7',246,72.46,'B1-B056',val='2k2',angle=90,fp=RES)
    s.wire(s.pt('U5',4),s.pt('R7',1));s.mark('U5',[4],'EE_DO');s.mark('R7',[1],'EE_DO');s.label('EE_DO',(232,72.46));s.net('R7',2,'EEDATA',5.08)
    pull(s,'R8',246,95,'B1-B065','FTDI_3V3','EE_DO')
    s.text('ORG=VCC: 128 x 16 words.\nEEDATA to DI; DO through 2k2.\n10k pull-up belongs on DO side.',170,136,1.15)
    # Reference-circuit capacitor population, intentionally omitting optional bulk after beads.
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    pull(s,'R14',270,194,'B1-B079','3V3_SYS','GW_VCP_RTS_N')
    s.symbol('SN74LV125APWR:SN74LV125APWR','U6',345,228,'B1-B016',unit=5,show=((361,213),(361,216),''))
    s.net('U6',14,'3V3_SYS',5.08,True);s.net('U6',7,'GND',5.08);cap(s,'C24',385,233,'B1-B036','100n','3V3_SYS')
    s.text('GW_* directions are from the MCU. TX/RX idle high; CTS_N inactive high.\nAll /OE pins directly use PWREN_N (ADR-040).\nThese four GW nets end at the next capture stage.',152,153,1.0)
    s.save()
    custom=copy.deepcopy(cache['Board1:FT232HL_BusPowered']);custom[1]='FT232HL_BusPowered'
    (OUT/'board1_symbols.kicad_sym').write_text('(kicad_symbol_lib (version 20220914) (generator ws_hardware_capture)\n'+dump(custom)+'\n)\n')
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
